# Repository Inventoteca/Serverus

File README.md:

# Serverus
Control de acceso IoT

El mismo dispositivo se ha adaptado para controlar otras cosas.  
Por ejemplo https://github.com/Inventoteca/Concentrador-IoT_MedidorTanque  

Otro ejemplo está en la carpeta "Nebulizador"  
https://randomnerdtutorials.com/esp8266-pinout-reference-gpios/  
https://randomnerdtutorials.com/esp8266-ds18b20-temperature-sensor-web-server-with-arduino-ide/  
https://randomnerdtutorials.com/esp8266-dht11dht22-temperature-and-humidity-web-server-with-arduino-ide/  

Diagrama simplificado (WIP)

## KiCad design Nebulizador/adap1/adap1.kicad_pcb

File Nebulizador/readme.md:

# Nebulizador
Serverus modificado para controlar un nebulizador.  

Se agregó una placa para colocar conectores y cables.  

GPIO utilizados  
5 Relay interno  
12 Relay externo o MOSFET  
14 Sensor DHT11, DHT22 o DS18B20

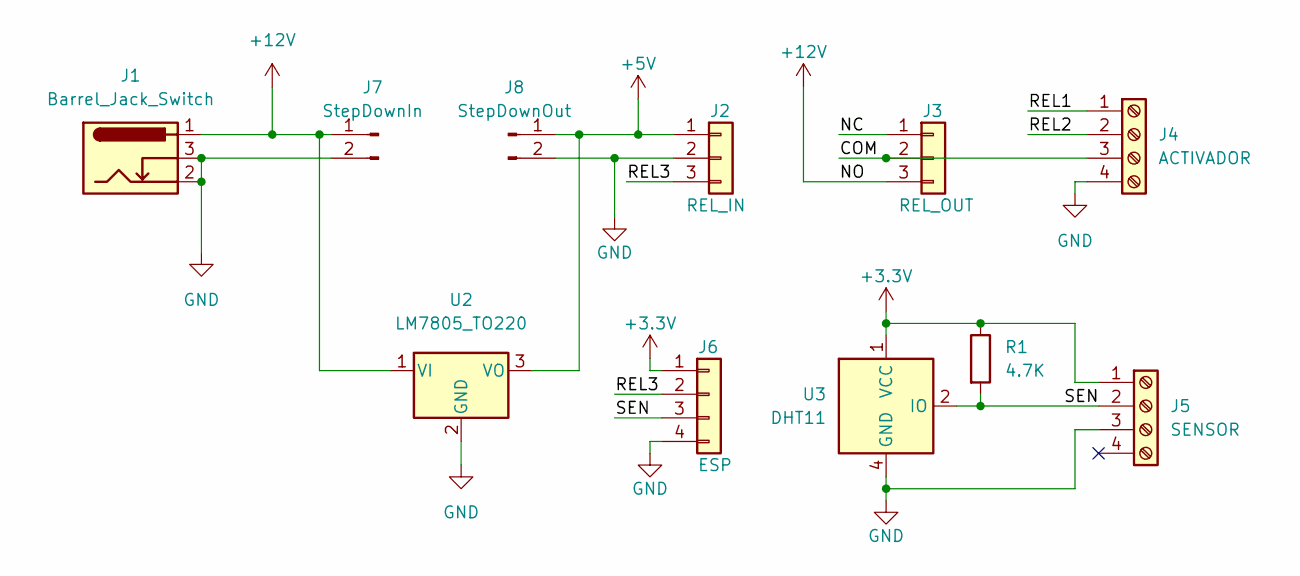
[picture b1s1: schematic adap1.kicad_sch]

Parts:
J1: Barrel_Jack_Switch; BarrelJack_CUI_PJ-102AH_Horizontal
J2: REL_IN; PinHeader_1x03_P2.54mm_Vertical
J3: REL_OUT; TerminalBlock_bornier-3_P5.08mm
J4: ACTIVADOR; TerminalBlock_bornier-4_P5.08mm
J5: SENSOR; TerminalBlock_bornier-4_P5.08mm
J6: ESP; PinHeader_1x04_P2.54mm_Vertical
J7: StepDownIn; PinSocket_1x02_P2.54mm_Vertical
J8: StepDownOut; PinSocket_1x02_P2.54mm_Vertical
R1: 4.7K; R_Axial_DIN0207_L6.3mm_D2.5mm_P7.62mm_Horizontal
U2: LM7805_TO220; TO-220-3_Vertical
U3: DHT11; Aosong_DHT11_5.5x12.0_P2.54mm

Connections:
+3.3V: J5.1, J6.1, R1.1, U3.1 (VCC)
+5V: J2.1, J8.1, U2.3 (VO)
+12V: J1.1, J3.3, J7.1, U2.1 (VI)
/COM: J3.2, J4.3
/NC: J3.1
/REL1: J4.1
/REL2: J4.2
/REL3: J2.3, J6.2
/SEN: J5.2, J6.3, R1.2, U3.2 (IO)
GND: J1.2, J1.3, J2.2, J4.4, J5.3, J6.4, J7.2, J8.2, U2.2 (GND), U3.4 (GND)

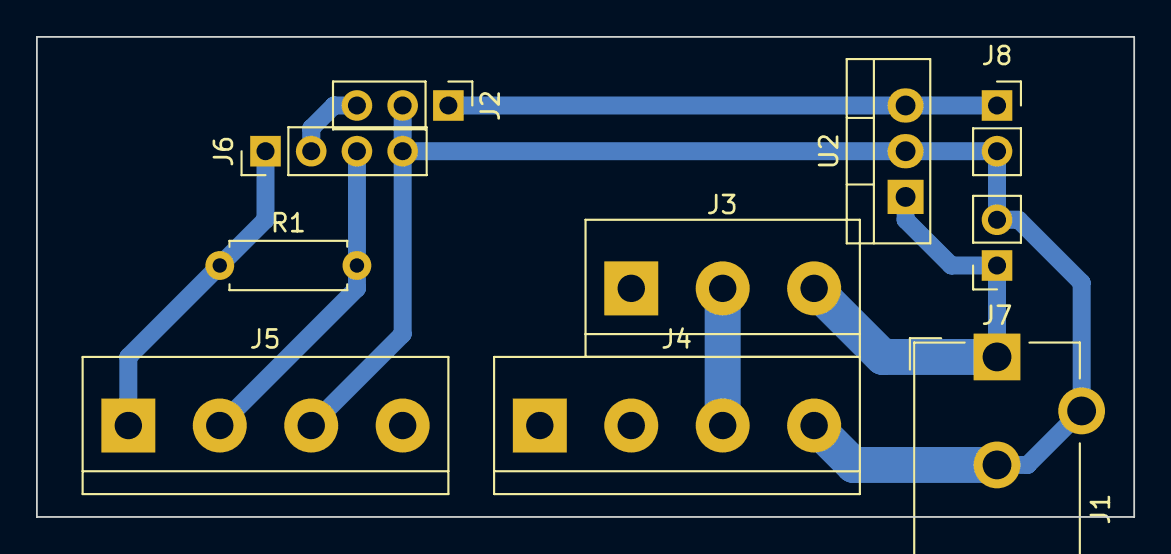
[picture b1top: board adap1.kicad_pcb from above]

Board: 2 copper layers, 61.0 x 26.7 mm, 10 parts (0 on the bottom side), 7 nets.

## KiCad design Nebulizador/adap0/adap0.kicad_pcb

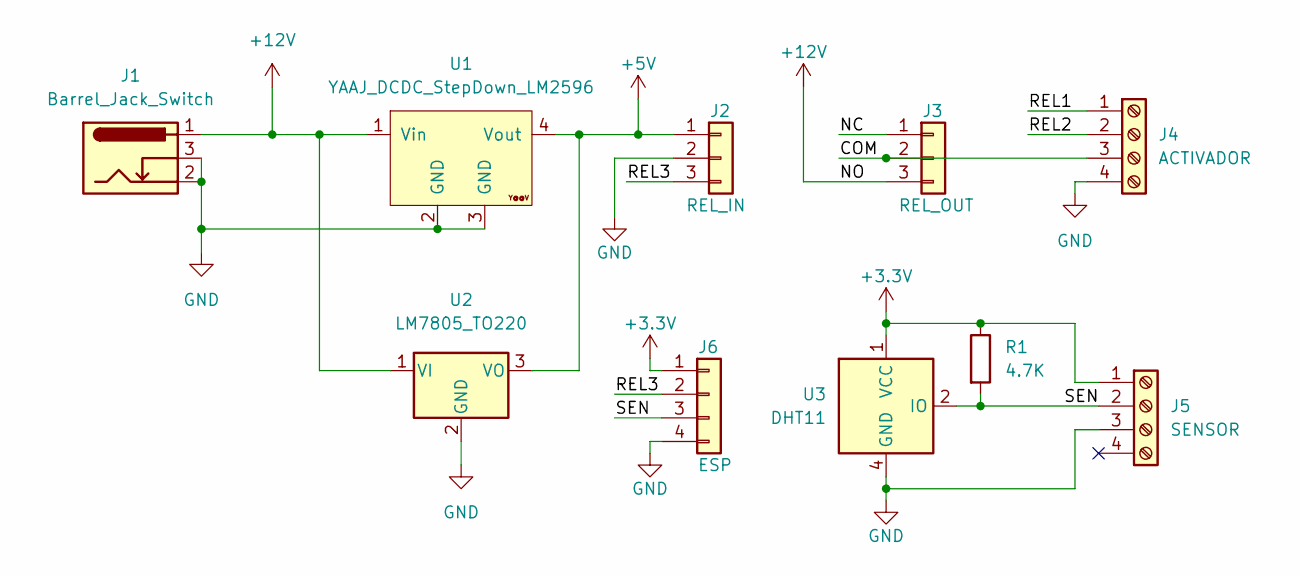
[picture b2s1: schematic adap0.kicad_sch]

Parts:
J1: Barrel_Jack_Switch; BarrelJack_CUI_PJ-102AH_Horizontal
J2: REL_IN; PinHeader_1x03_P2.54mm_Vertical
J3: REL_OUT; TerminalBlock_bornier-3_P5.08mm
J4: ACTIVADOR; TerminalBlock_bornier-4_P5.08mm
J5: SENSOR; TerminalBlock_bornier-4_P5.08mm
J6: ESP; PinHeader_1x04_P2.54mm_Vertical
R1: 4.7K; R_Axial_DIN0207_L6.3mm_D2.5mm_P7.62mm_Horizontal
U1: YAAJ_DCDC_StepDown_LM2596
U2: LM7805_TO220; TO-220-3_Vertical
U3: DHT11; Aosong_DHT11_5.5x12.0_P2.54mm

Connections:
+3.3V: J5.1, J6.1, R1.1, U3.1 (VCC)
+5V: J2.1, U1.4 (Vout), U2.3 (VO)
+12V: J1.1, J3.3, U1.1 (Vin), U2.1 (VI)
/COM: J3.2, J4.3
/NC: J3.1
/REL1: J4.1
/REL2: J4.2
/REL3: J2.3, J6.2
/SEN: J5.2, J6.3, R1.2, U3.2 (IO)
GND: J1.2, J1.3, J2.2, J4.4, J5.3, J6.4, U1.2 (GND), U1.3 (GND), U2.2 (GND), U3.4 (GND)

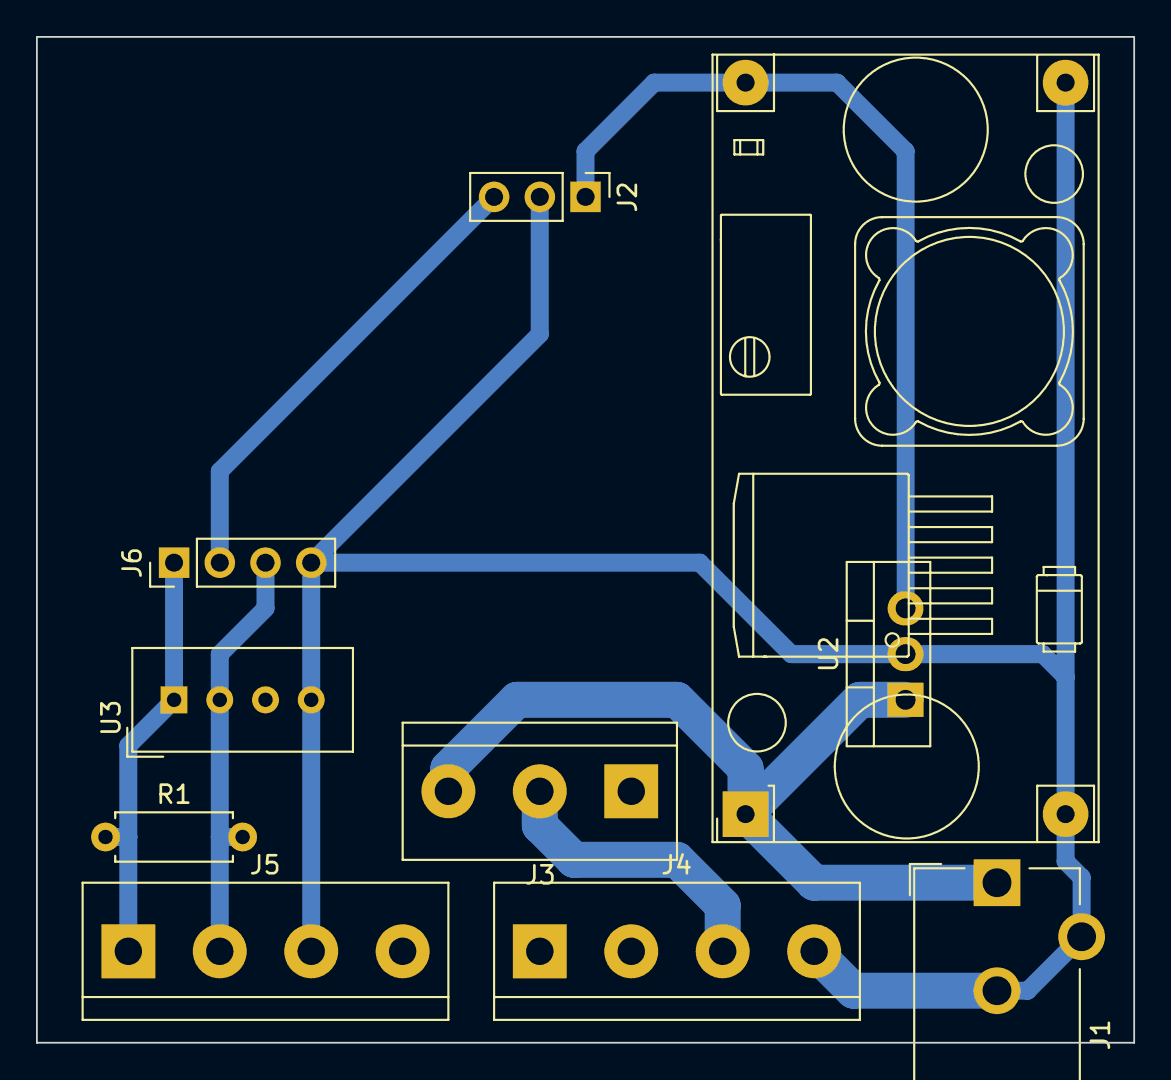
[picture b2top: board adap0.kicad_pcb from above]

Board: 2 copper layers, 61.0 x 55.9 mm, 10 parts (0 on the bottom side), 7 nets.

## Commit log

2022-09-23 Actualizar readme
2022-09-23 Crear diseño nebulizador
2022-09-25 componentes y pistas, versión 1 para maquinado
2022-09-29 actualizar proyectos de kicad y diagrama simplificado
2022-09-29 agregar readme e imágenes
